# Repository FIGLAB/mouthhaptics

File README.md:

# Mouth Haptics

Open source code for <a href="https://dl.acm.org/doi/10.1145/3491102.3501960"> Mouth Haptics in VR using a Heaset Ultrasound Phased Array </a>.
This paper was published in and received Best Paper Award at CHI 2022.
Contact me with questions <a href="vivian-shen.com">here</a>!

### Repository Contents
 - PCB\_files: contains the PCB files for the paper prototype and future work iterations.
 - simulator: all of the Unity code for MouthHaptics

### Assembly Instructions

<a href="https://docs.google.com/spreadsheets/d/19ZBoKU5TYJbX7AsaLpiNlDs6BuEZi-PdD4ZHkbttzh4/edit?usp=sharing">Bill of Materials</a>

#### Step 1: Assemble driver board

Assemble the Ultraino driver board following <a href="www.instructables.com/Ultrasonic-Array/">these instructions</a>

#### Step 2: Assemble the Ultrasound array

- First, determine the polarity of every transducer. You can do this with an oscilloscope + function generator or <a href="https://www.youtube.com/watch?v=0HaKv3aJQWA">a multimeter</a>.
- Solder the female MOLEX connectors onto the PCB. You can use any combination of normal/right angle MOLEX connector.
- Create ribbon cables with two male MOLEX ends, to connect the two PCBs.
- Insert all transducers into the holes - solder to attach. Make sure the transducers are all the same polarity in the same direction.
- Connect all the ribbon cablues between the driver board and the array.

#### Step 3: Set up Unity Software

Clone (or Fork!) this repository

``` 
git clone https://github.com/FIGLAB/IMUPoser.git
```
 
Once you have the Unity hub installed, you should be able to open the simulator unity project. The demos are all in the Scenes folder.

## License

This work is licensed under a GPL v 2.0 License file present in the repo. Please contact innovation@cmu.edu if you would like another license for your use.

## Reference

Vivian Shen, Craig Shultz, and Chris Harrison. 2022. Mouth Haptics in VR Using a Headset Ultrasound Phased Array. In Proceedings of the 2022 CHI Conference on Human Factors in Computing Systems (New Orleans, LA, USA) (CHI ’22). Association for Computing Machinery, New York, NY, USA, Article 275, 14 pages. https://doi.org/10.1145/3491102.3501960

BibTex Reference:
```
@inproceedings{shen2022mouth,
  title={Mouth Haptics in VR using a Headset Ultrasound Phased Array},
  author={Shen, Vivian and Shultz, Craig and Harrison, Chris},
  booktitle={CHI Conference on Human Factors in Computing Systems},
  pages={1--14},
  year={2022}
}
```

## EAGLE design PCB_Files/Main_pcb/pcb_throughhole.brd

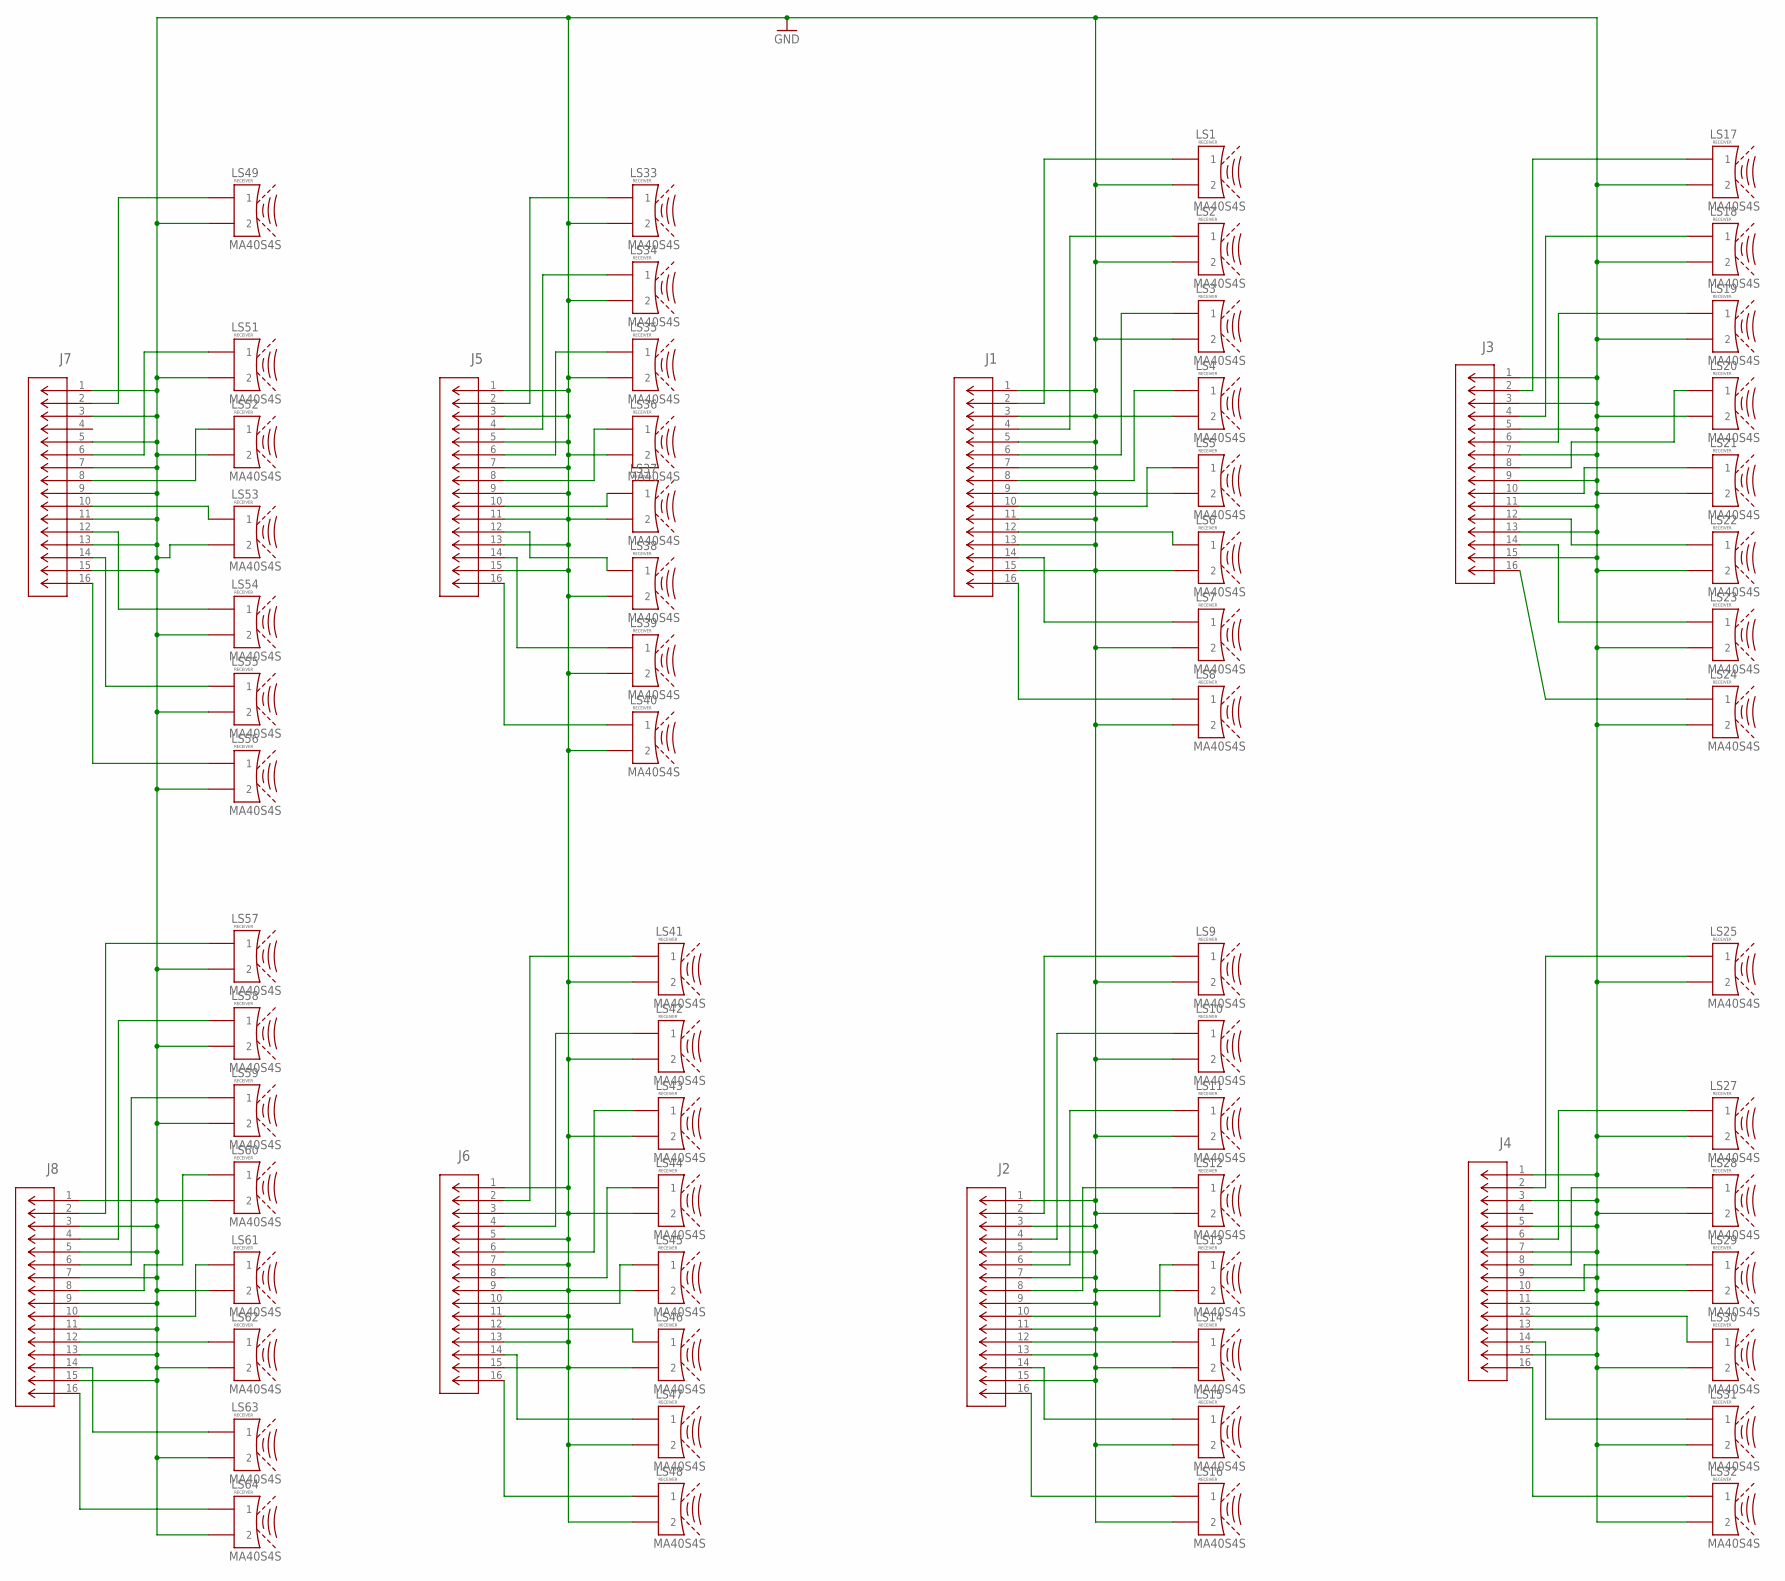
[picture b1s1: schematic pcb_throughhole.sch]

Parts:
J1, J2, J3, J4, J5, J6, J7, J8: 70246-1201; CONN_70246-1201_MOL
LS1, LS2, LS3, LS4, LS5, LS6, LS7, LS8, LS9, LS10, LS11, LS12, LS13, LS14, LS15, LS16, LS17, LS18, LS19, LS20, LS21, LS22, LS23, LS24, LS25, LS27, LS28, LS29, LS30, LS31, LS32, LS33, LS34, LS35, LS36, LS37, LS38, LS39, LS40, LS41, LS42, LS43, LS44, LS45, LS46, LS47, LS48, LS49, LS51, LS52, LS53, LS54, LS55, LS56, LS57, LS58, LS59, LS60, LS61, LS62, LS63, LS64: MA40S4S; XDCR_MA40S4S

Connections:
GND: J1.1, J1.3, J1.5, J1.7, J1.9, J1.11, J1.13, J1.15, J2.1, J2.3, J2.5, J2.7, J2.9, J2.11, J2.13, J2.15, J3.1, J3.3, J3.5, J3.7, J3.9, J3.11, J3.13, J3.15, J4.1, J4.3, J4.5, J4.7, J4.9, J4.11, J4.13, J4.15, J5.1, J5.3, J5.5, J5.7, J5.9, J5.11, J5.13, J5.15, J6.1, J6.3, J6.5, J6.7, J6.9, J6.11, J6.13, J6.15, J7.1, J7.3, J7.5, J7.7, J7.9, J7.11, J7.13, J7.15, J8.1, J8.3, J8.5, J8.7, J8.9, J8.11, J8.13, J8.15, LS1.2, LS2.2, LS3.2, LS4.2, LS5.2, LS6.2, LS7.2, LS8.2, LS9.2, LS10.2, LS11.2, LS12.2, LS13.2, LS14.2, LS15.2, LS16.2, LS17.2, LS18.2, LS19.2, LS20.2, LS21.2, LS22.2, LS23.2, LS24.2, LS25.2, LS27.2, LS28.2, LS29.2, LS30.2, LS31.2, LS32.2, LS33.2, LS34.2, LS35.2, LS36.2, LS37.2, LS38.2, LS39.2, LS40.2, LS41.2, LS42.2, LS43.2, LS44.2, LS45.2, LS46.2, LS47.2, LS48.2, LS49.2, LS51.2, LS52.2, LS53.2, LS54.2, LS55.2, LS56.2, LS57.2, LS58.2, LS59.2, LS60.2, LS61.2, LS62.2, LS63.2, LS64.2
unnamed: J1.16, LS8.1
unnamed: J1.14, LS7.1
unnamed: J1.12, LS6.1
unnamed: J1.10, LS5.1
unnamed: J1.8, LS4.1
unnamed: J1.6, LS3.1
unnamed: J1.4, LS2.1
unnamed: J1.2, LS1.1
unnamed: J2.16, LS16.1
unnamed: J2.14, LS15.1
unnamed: J2.12, LS14.1
unnamed: J2.10, LS13.1
unnamed: J2.8, LS12.1
unnamed: J2.6, LS11.1
unnamed: J2.4, LS10.1
unnamed: J2.2, LS9.1
unnamed: J4.16, LS32.1
unnamed: J4.14, LS31.1
unnamed: J4.12, LS30.1
unnamed: J4.10, LS29.1
unnamed: J4.8, LS28.1
unnamed: J4.6, LS27.1
unnamed: J4.2, LS25.1
unnamed: J3.16, LS24.1
unnamed: J3.14, LS23.1
unnamed: J3.12, LS22.1
unnamed: J3.10, LS21.1
unnamed: J3.8, LS20.1
unnamed: J3.6, LS19.1
unnamed: J3.4, LS18.1
unnamed: J3.2, LS17.1
unnamed: J5.16, LS40.1
unnamed: J5.14, LS39.1
unnamed: J5.12, LS38.1
unnamed: J5.10, LS37.1
unnamed: J5.8, LS36.1
unnamed: J5.6, LS35.1
unnamed: J5.4, LS34.1
unnamed: J5.2, LS33.1
unnamed: J6.16, LS48.1
unnamed: J6.14, LS47.1
unnamed: J6.12, LS46.1
unnamed: J6.10, LS45.1
unnamed: J6.8, LS44.1
unnamed: J6.6, LS43.1
unnamed: J6.4, LS42.1
unnamed: J6.2, LS41.1
unnamed: J8.16, LS64.1
unnamed: J8.14, LS63.1
unnamed: J8.12, LS62.1
unnamed: J8.10, LS61.1
unnamed: J8.8, LS60.1
unnamed: J8.6, LS59.1
unnamed: J8.4, LS58.1
unnamed: J8.2, LS57.1
unnamed: J7.16, LS56.1
unnamed: J7.14, LS55.1
unnamed: J7.12, LS54.1
unnamed: J7.10, LS53.1
unnamed: J7.8, LS52.1
unnamed: J7.6, LS51.1
unnamed: J7.2, LS49.1

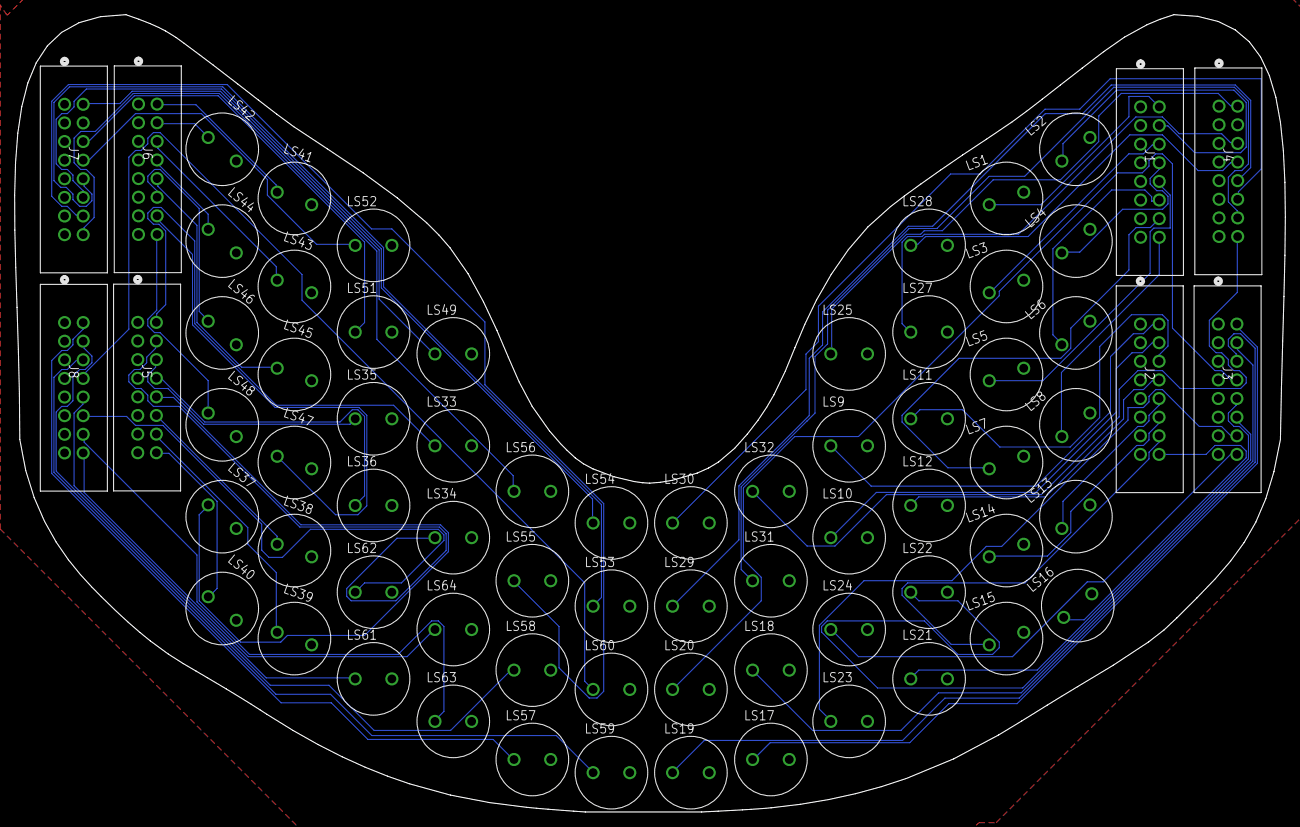
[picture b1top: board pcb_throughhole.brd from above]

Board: 2 copper layers, 173.3 x 108.7 mm, 70 parts (0 on the bottom side), 63 nets.

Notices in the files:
parts and their libraries:
COPYRIGHT: Copyright (C) 2018 Accelerated Designs. All rights reserved
